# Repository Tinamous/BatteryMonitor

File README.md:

Internet Of Things Remote System Monitor
========================================

For remote locations a battery powered devices may be the only realistic way of powering equipment, these may be left to work for months or years until one day the battery dies or goes flat unexpectedly or something else happens.

This project uses the Sigfox Arduino MKR FOX 1200 to provide low power wireless internet connectivity and a INA219 to monitor the battery. This allows monitor and early notification of problems.

Additionally 2x latching relays, 3x N-Channel fets and some digital/analog inputs provide means to monitor other parts of a system as well (e.g. monitor switches, water levels, control pumps, lights etc.).

The system is composed of:

* Arduino MKR FOX 1200 Sigfox based Arduino.
* INA219 power monitor (0R1 resistor - limited to 2A due to package size).
* 2x Latching relays for output and charger input.
* 3x N-Channel FET outputs.
* 6x Analog input connectors (4x 3 pin with GND, 3v3 and signal, 1x 4 pin with GND 5V and 2x signal divided to allow 5V analog).
* On-board 5V buck regulator from the battery.
* On-board 3v3 regulator for relay and analog connectors.
* Mini prototyping area.
* Always on USB A power output.

Primary Use Case - Garage
=========================

* 12V Lead Acid Battery (i.e. car battery) connected to the battery input
* Powered system connected to the output (humidity controlled boxes).
* Solar charger connected to charger connector.
* LED lighting connected to FET1, 2 and 3.

Alternative Usages:
* The battery connector can be used as an output with inputs from 2 batteries or a power supply and battery allowing a backup power source to be switched in should the primary fall out of acceptable range. In this case the power measurement is purely for output and does not include power used through the FET outputs, analog inputs or the system itself.

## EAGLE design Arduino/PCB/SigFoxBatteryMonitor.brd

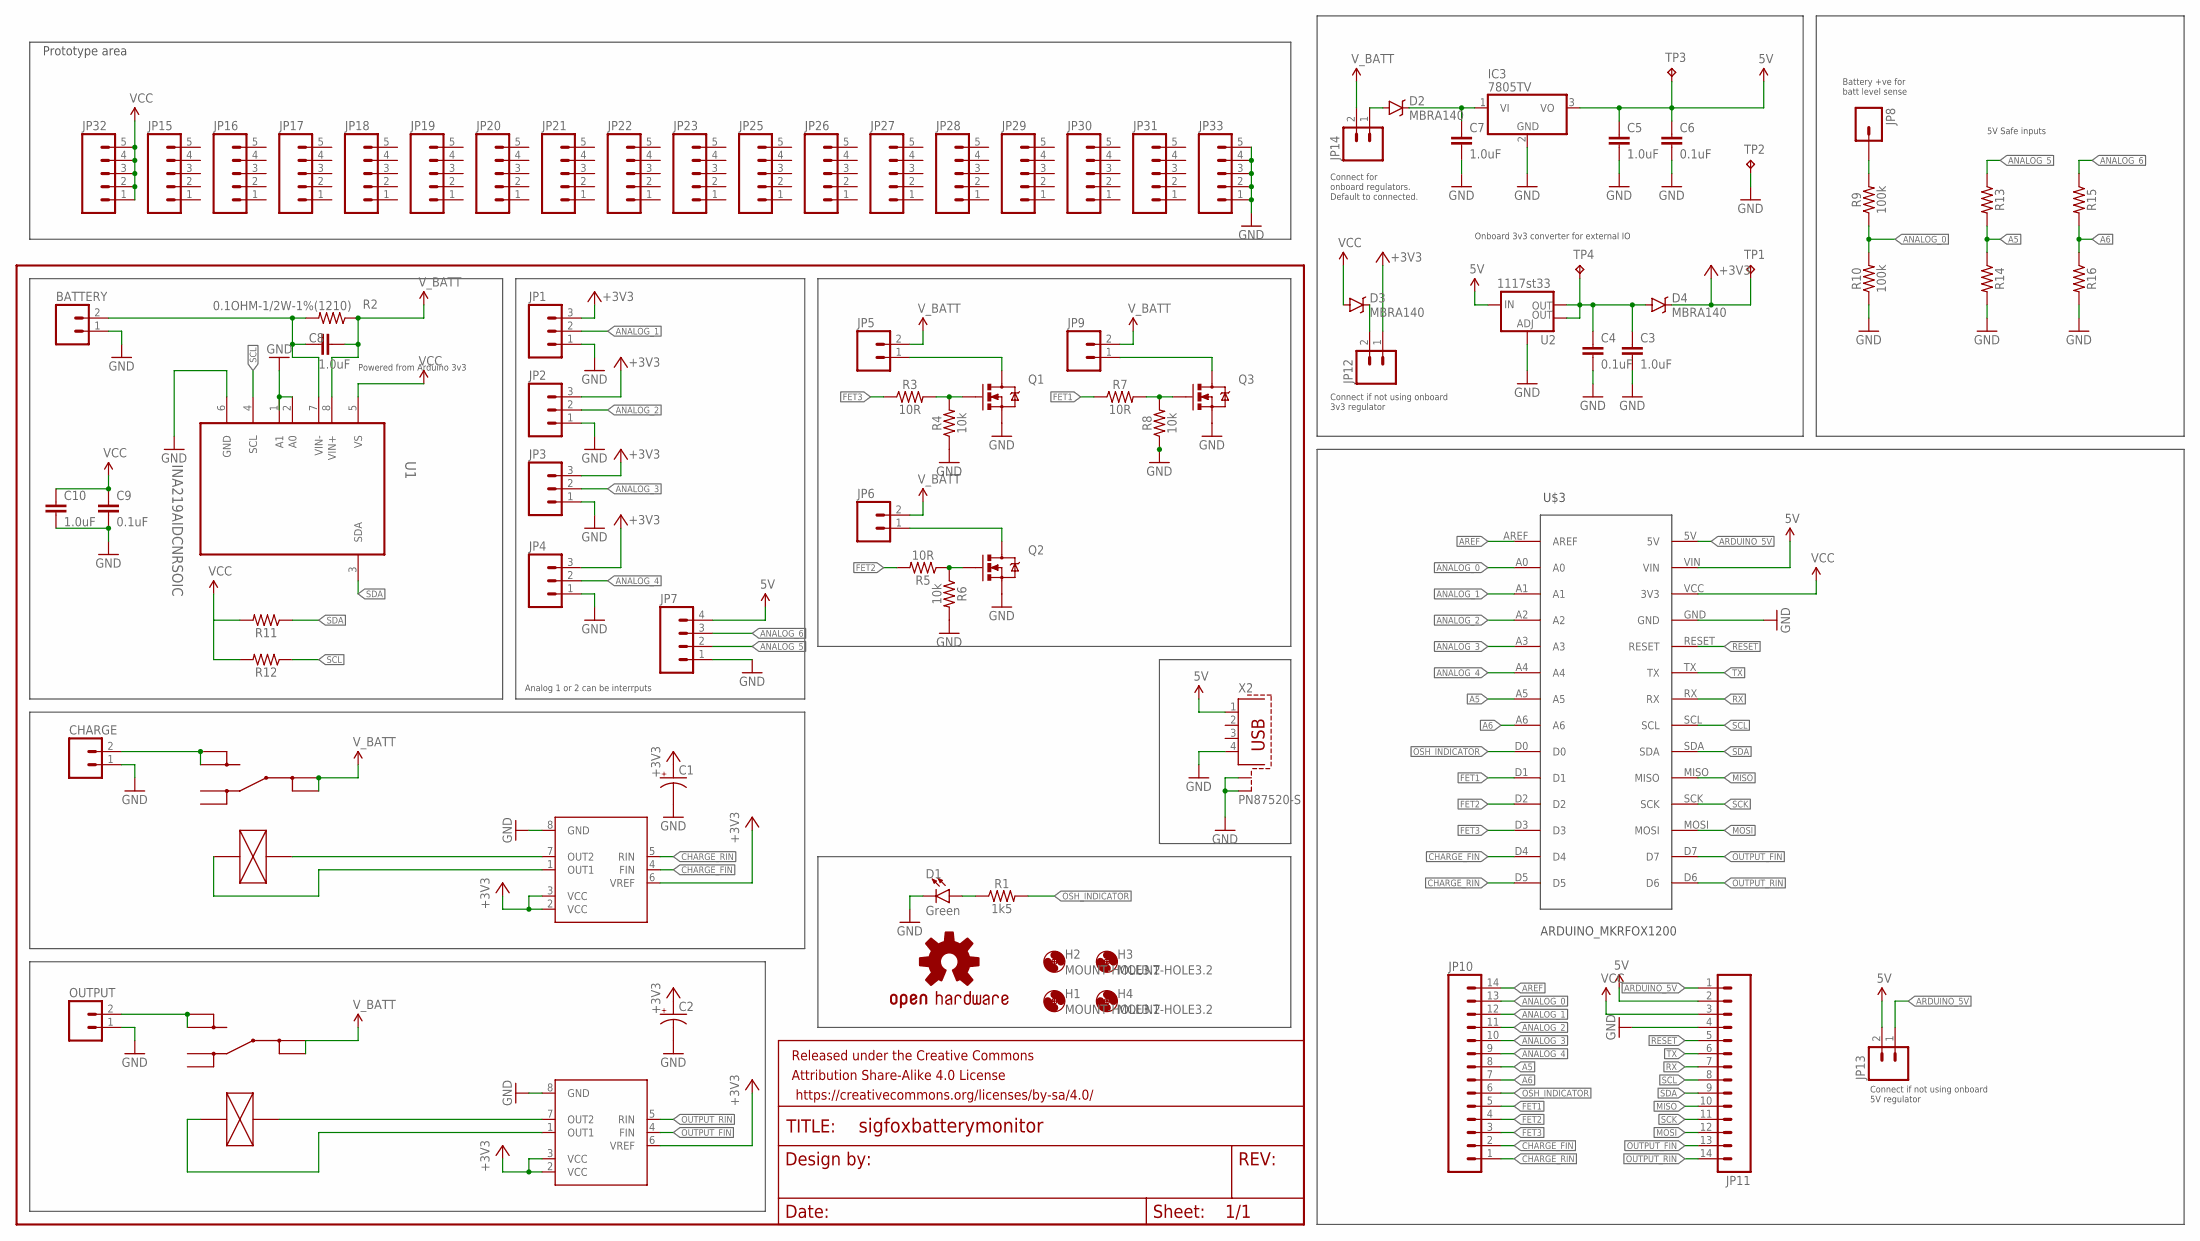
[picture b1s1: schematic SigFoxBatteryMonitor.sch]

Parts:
BATTERY: M025MM; SCREWTERMINAL-5MM-2; FARNELL 2493689
C1, C2: CAP_POL1206; EIA3216; FARNELL 1457413
C3, C5, C7, C8, C10: 1.0uF; 0805
C4, C6, C9: 0.1uF; 0805
CHARGE: M025MM; SCREWTERMINAL-5MM-2; FARNELL 2493689
D1: Green; LED-1206-BOTTOM
D2, D3, D4: MBRA140; SMA-DIODE
FRAME1: FRAME-LETTER; CREATIVE_COMMONS
H1, H2, H3, H4: MOUNT-HOLE3.2; 3,2
IC1, IC2: BD6211F; SOP8; FARNELL 1716256
IC3: 7805TV; TO220V
JP1, JP2, JP3, JP4: M03POLAR; MOLEX-1X3
JP5, JP6, JP9: M02POLAR; MOLEX-1X2
JP7: M04POLAR; MOLEX-1X4
JP8: M01PTH; 1X01
JP10, JP11: M14; 1X14
JP12, JP13, JP14: M02PTH; 1X02
JP15, JP16, JP17, JP18, JP19, JP20, JP21, JP22, JP23, JP25, JP26, JP27, JP28, JP29, JP30, JP31: M05NO_SILK; 1X05_NO_SILK
JP32, JP33: M05PTH; 1X05
LOGO1: OSHW-LOGOM; OSHW-LOGO-M
OUTPUT: M025MM; SCREWTERMINAL-5MM-2; FARNELL 2493689
Q1, Q2, Q3: IRF7413Z; SO08; FARNELL 2468020
R1: 1k5; 1206
R2: 0.1OHM-1/2W-1%(1210); 1210
R3, R5, R7: 10R; 0805
R4, R6, R8: 10k; 0805
R9, R10: 100k; 0805
R11, R12, R13, R14, R15, R16: 0805
TP1: 3v3; TP15R
TP2: GND; TP15R
TP3, TP4: 5v; TP15R
U1: INA219AIDCNRSOIC; SO08
U2: 1117st33; SOT223; FARNELL 1652366
U$1, U$2: RELAY_G5RL-1E; G5RL-1E; FARNELL 2432863
U$3: ARDUINO_MKRFOX1200
X2: PN87520-S

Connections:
5V: C5.1, C6.1, IC3.3 (VO), JP7.4, JP11.2, JP13.2, TP3.TP, U2.3 (IN), U$3.VIN, X2.1
+3V3: C1.A (+), C2.A (+), D4.C, IC1.2 (VCC), IC1.3 (VCC), IC1.6 (VREF), IC2.2 (VCC), IC2.3 (VCC), IC2.6 (VREF), JP1.3, JP2.3, JP3.3, JP4.3, JP12.1, TP1.TP
A5: JP10.8, R13.2, R14.1, U$3.A5
A6: JP10.7, R15.2, R16.1, U$3.A6
ANALOG_0: JP10.13, R9.1, R10.2, U$3.A0
ANALOG_1: JP1.2, JP10.12, U$3.A1
ANALOG_2: JP2.2, JP10.11, U$3.A2
ANALOG_3: JP3.2, JP10.10, U$3.A3
ANALOG_4: JP4.2, JP10.9, U$3.A4
ANALOG_5: JP7.2, R13.1
ANALOG_6: JP7.3, R15.1
ARDUINO_5V: JP11.1, JP13.1, U$3.5V
AREF: JP10.14, U$3.AREF
CHARGE_FIN: IC1.4 (FIN), JP10.2, U$3.D4
CHARGE_RIN: IC1.5 (RIN), JP10.1, U$3.D5
FET1: JP10.5, R7.1, U$3.D1
FET2: JP10.4, R5.2, U$3.D2
FET3: JP10.3, R3.1, U$3.D3
GND: BATTERY.1, C1.C (-), C2.C (-), C3.2, C4.2, C5.2, C6.2, C7.2, C9.2, C10.2, CHARGE.1, D1.C, IC1.8 (GND), IC2.8 (GND), IC3.2 (GND), JP1.1, JP2.1, JP3.1, JP4.1, JP7.1, JP11.4, JP33.1, JP33.2, JP33.3, JP33.4, JP33.5, OUTPUT.1, Q1.1 (S), Q1.2 (S), Q1.3 (S), Q2.1 (S), Q2.2 (S), Q2.3 (S), Q3.1 (S), Q3.2 (S), Q3.3 (S), R4.1, R6.2, R8.1, R10.1, R14.2, R16.2, TP2.TP, U1.1 (A1), U1.2 (A0), U1.6 (GND), U2.1 (ADJ), U$3.GND, X2.4, X2.S1, X2.S2
MISO: JP11.10, U$3.MISO
MOSI: JP11.12, U$3.MOSI
unnamed: D1.A, R1.1
unnamed: OUTPUT.2, U$1.NO@1 (NO), U$1.NO@2 (NO)
unnamed: CHARGE.2, U$2.NO@1 (NO), U$2.NO@2 (NO)
unnamed: Q1.4 (G), R3.2, R4.2
unnamed: JP5.1, Q1.5 (D), Q1.6 (D), Q1.7 (D), Q1.8 (D)
unnamed: Q3.4 (G), R7.2, R8.2
unnamed: BATTERY.2, C8.1, R2.2, U1.7 (VIN-)
unnamed: IC2.7 (OUT2), U$1.COIL-
unnamed: IC2.1 (OUT1), U$1.COIL+
unnamed: IC1.7 (OUT2), U$2.COIL-
unnamed: IC1.1 (OUT1), U$2.COIL+
unnamed: Q2.4 (G), R5.1, R6.1
unnamed: JP9.1, Q3.5 (D), Q3.6 (D), Q3.7 (D), Q3.8 (D)
unnamed: D3.C, JP12.2
unnamed: JP6.1, Q2.5 (D), Q2.6 (D), Q2.7 (D), Q2.8 (D)
unnamed: JP8.1, R9.2
unnamed: C7.1, D2.C, IC3.1 (VI)
unnamed: D2.A, JP14.1
unnamed: C3.1, C4.1, D4.A, TP4.TP, U2.2 (OUT), U2.4 (OUT)
OSH_INDICATOR: JP10.6, R1.2, U$3.D0
OUTPUT_FIN: IC2.4 (FIN), JP11.13, U$3.D7
OUTPUT_RIN: IC2.5 (RIN), JP11.14, U$3.D6
RESET: JP11.5, U$3.RESET
RX: JP11.7, U$3.RX
SCK: JP11.11, U$3.SCK
SCL: JP11.8, R12.1, U1.4 (SCL), U$3.SCL
SDA: JP11.9, R11.1, U1.3 (SDA), U$3.SDA
TX: JP11.6, U$3.TX
VCC: C9.1, C10.1, D3.A, JP11.3, JP32.1, JP32.2, JP32.3, JP32.4, JP32.5, R11.2, R12.2, U1.5 (VS), U$3.VCC (3V3)
V_BATT: C8.2, JP5.2, JP6.2, JP9.2, JP14.2, R2.1, U1.8 (VIN+), U$1.COM@1 (COM), U$1.COM@2 (COM), U$2.COM@1 (COM), U$2.COM@2 (COM)

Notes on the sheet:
Onboard 3v3 converter for external IO
Powered from Arduino 3v3
Battery +ve for batt level sense
Connect if not using onboard 5V regulator
Connect if not using onboard 3v3 regulator
Connect for onboard regulators. Default to connected.
5V Safe inputs
Analog 1 or 2 can be interrputs
Prototype area

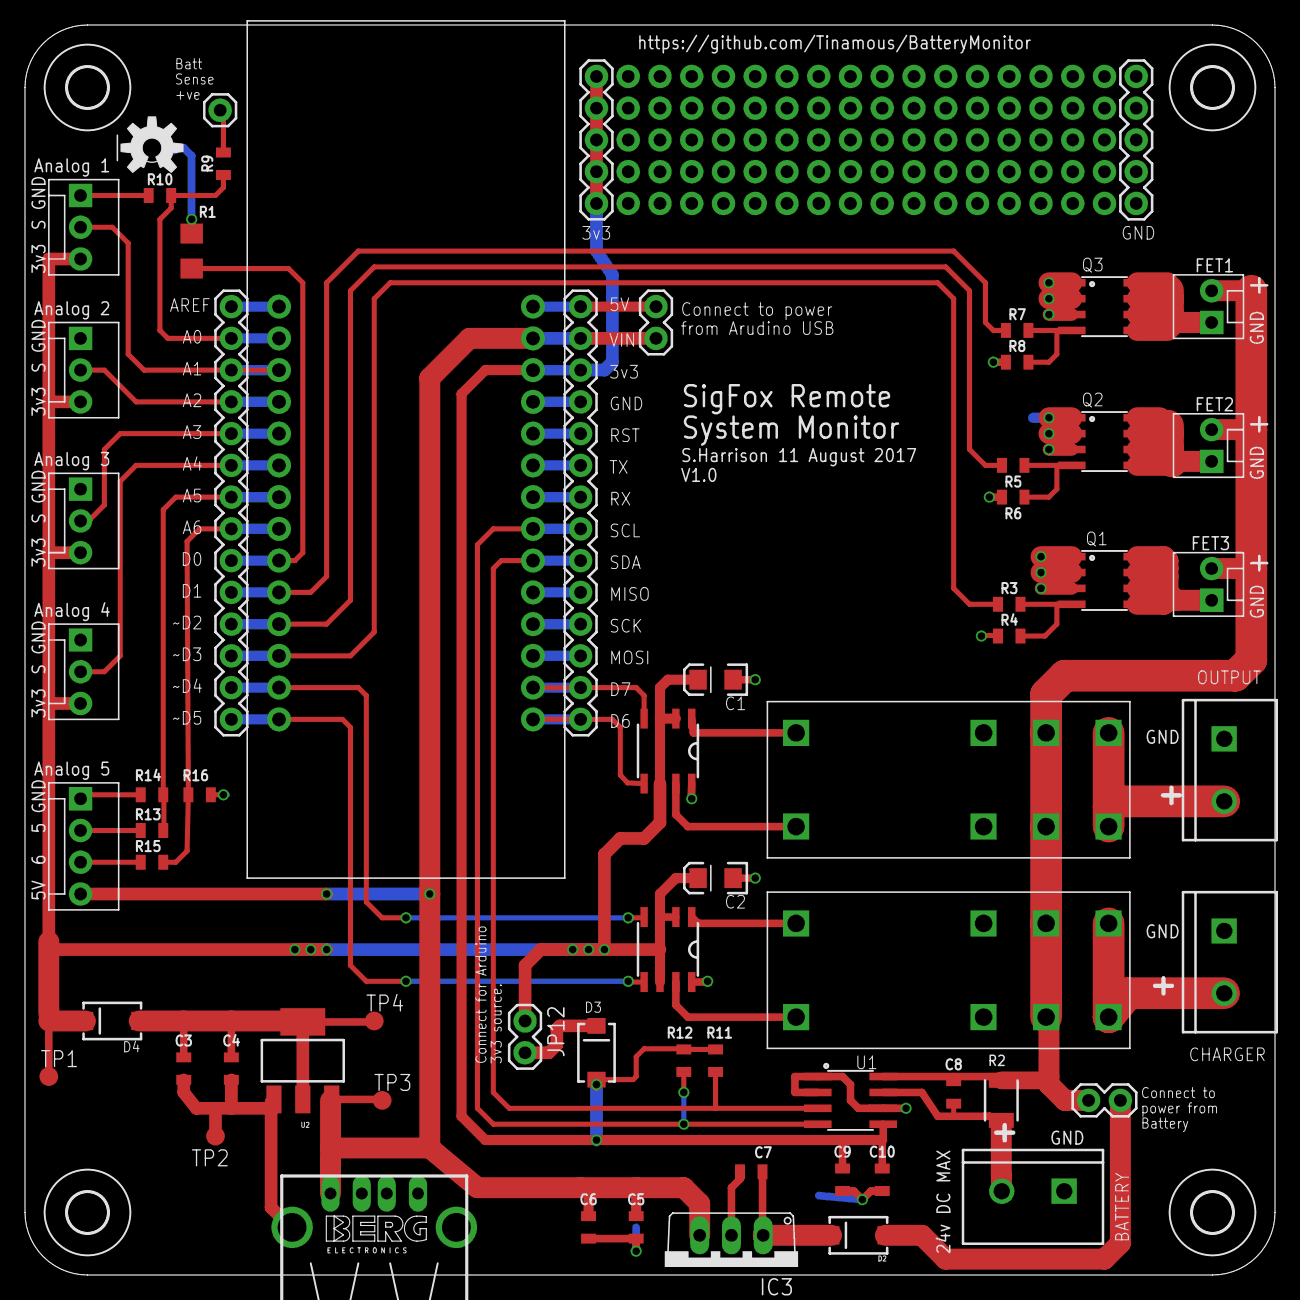
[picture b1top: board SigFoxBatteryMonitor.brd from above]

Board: 2 copper layers, 100.0 x 100.0 mm, 87 parts (1 on the bottom side), 51 nets.

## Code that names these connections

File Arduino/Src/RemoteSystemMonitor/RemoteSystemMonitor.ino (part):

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
void setup() {
  pinMode(0, OUTPUT); // led
  pinMode(1, OUTPUT); // Fet1
  pinMode(2, OUTPUT); // Fet2
  pinMode(3, OUTPUT); // Fet3
  pinMode(4, OUTPUT); // charge relay FIN
  pinMode(5, OUTPUT); // charge relay RIN
  pinMode(6, OUTPUT); // output relay FIN
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
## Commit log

2017-08-11 Added readme
2017-08-11 Start of Arduino MKRFOX1200 based battery monitor
2017-09-03 Version 1.0 PCB.
2017-09-17 Added customisable case
2017-09-17 Updated readme a bit.
2017-11-15 Fixed type on silkscreen and improved layout of schematic.
2017-11-15 Minor working improvement for readme.
2017-11-15 Adding arduino code.
2017-11-15 Improvements to the enslosure
2017-11-15 Improved formatting slightly
2017-11-15 Added images
2017-11-15 Fixed typo

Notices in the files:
parts and their libraries:
SparkFun-Connectors: Licensing: Creative Commons ShareAlike 4.0 International - https://creativecommons.org/licenses/by-sa/4.0
SparkFun-Aesthetics: Released under the Creative Commons Attribution Share-Alike 4.0 License
SparkFun-Aesthetics: https://creativecommons.org/licenses/by-sa/4.0
